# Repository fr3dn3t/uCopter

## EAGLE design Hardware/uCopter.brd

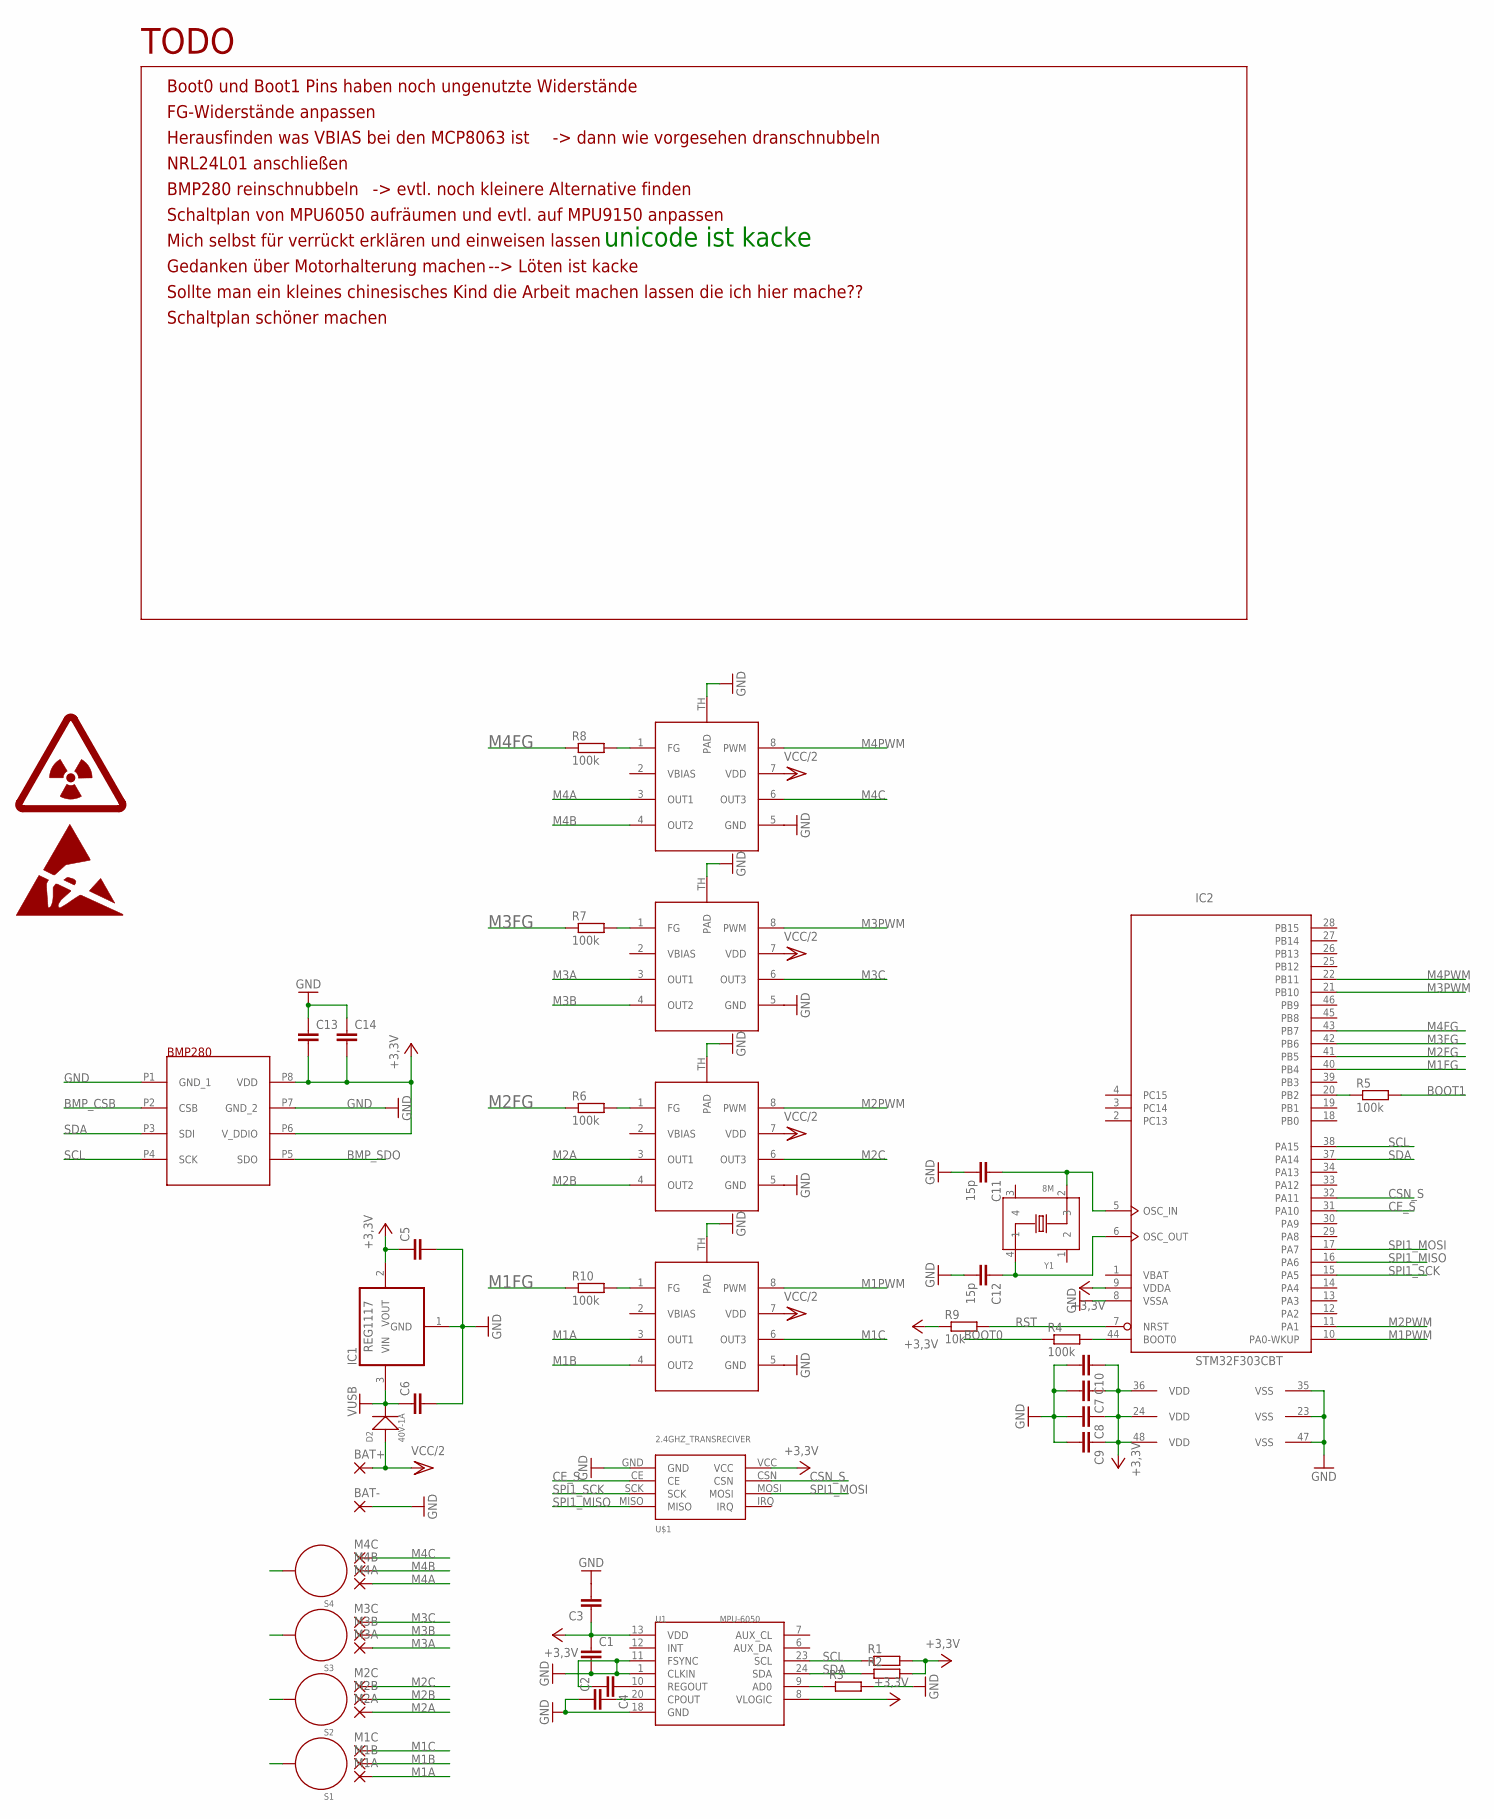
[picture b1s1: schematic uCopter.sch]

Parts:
BAT+: SMD2; SMD1,27-2,54
BAT-: SMD2; SMD1,27-2,54
C1, C2, C3, C4, C7, C8, C9, C10, C13, C14: C-EUC0402; C0402
C5, C6: C-EUC0603; C0603
C11, C12: 15p; C0402
D2: 40V-1A; DO-214AC
IC1: REG1117; SOT223
IC2: STM32F303CBT; LQFP48
M1A, M1B, M1C, M2A, M2B, M2C, M3A, M3B, M3C, M4A, M4B, M4C: 2,15/1,0
R1, R2, R3: R-EU_R0402; R0402
R4, R5, R6, R7, R8, R10: 100k; R0402
R9: 10k; R0402
S1, S2, S3, S4: STANDOFF_ELECTRICAL; STANDOFF-ELECTRICAL
T1: BMP280
U1: MPU-6050; QFN24G-0.5-4X4MM
U$1: 2.4GHZ_TRANSRECIVER
U$6, U$7, U$8, U$9: MCP8063; DFN8-4X4
Y1: 8M; X4-SMD-3.2X2.5X0.7MM

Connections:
+3,3V: C1.1, C3.1, C5.1, C7.1, C8.1, C9.1, C10.1, C13.2, C14.2, IC1.2 (VOUT), IC2.9 (VDDA), IC2.24 (VDD), IC2.36 (VDD), IC2.48 (VDD), R1.2, R2.2, R9.1, T1.P6 (V_DDIO), T1.P8 (VDD), U1.8 (VLOGIC), U1.13 (VDD), U$1.VCC
BMP_CSB: T1.P2 (CSB)
BMP_SDO: T1.P5 (SDO)
BOOT0: R4.1
BOOT1: R5.2
CE_S: IC2.31 (PA10), U$1.CE
CSN_S: IC2.32 (PA11), U$1.CSN
GND: BAT-.1, C1.2, C2.1, C3.2, C4.2, C5.2, C6.2, C7.2, C8.2, C9.2, C10.2, C11.2, C12.2, C13.1, C14.1, IC1.1 (GND), IC2.8 (VSSA), IC2.23 (VSS), IC2.35 (VSS), IC2.47 (VSS), R3.2, T1.P1 (GND_1), T1.P7 (GND_2), U1.1 (CLKIN), U1.11 (FSYNC), U1.18 (GND), U$1.GND, U$6.5 (GND), U$6.TH (PAD), U$7.5 (GND), U$7.TH (PAD), U$8.5 (GND), U$8.TH (PAD), U$9.5 (GND), U$9.TH (PAD)
M1A: M1A.1, U$6.3 (OUT1)
M1B: M1B.1, U$6.4 (OUT2)
M1C: M1C.1, U$6.6 (OUT3)
M1FG: IC2.40 (PB4), R10.1
M1PWM: IC2.10 (PA0-WKUP), U$6.8 (PWM)
M2A: M2A.1, U$7.3 (OUT1)
M2B: M2B.1, U$7.4 (OUT2)
M2C: M2C.1, U$7.6 (OUT3)
M2FG: IC2.41 (PB5), R6.1
M2PWM: IC2.11 (PA1), U$7.8 (PWM)
M3A: M3A.1, U$8.3 (OUT1)
M3B: M3B.1, U$8.4 (OUT2)
M3C: M3C.1, U$8.6 (OUT3)
M3FG: IC2.42 (PB6), R7.1
M3PWM: IC2.21 (PB10), U$8.8 (PWM)
M4A: M4A.1, U$9.3 (OUT1)
M4B: M4B.1, U$9.4 (OUT2)
M4C: M4C.1, U$9.6 (OUT3)
M4FG: IC2.43 (PB7), R8.1
M4PWM: IC2.22 (PB11), U$9.8 (PWM)
unnamed: R7.2, U$8.1 (FG)
unnamed: R8.2, U$9.1 (FG)
unnamed: C4.1, U1.10 (REGOUT)
unnamed: C2.2, U1.20 (CPOUT)
unnamed: R3.1, U1.9 (AD0)
unnamed: IC2.44 (BOOT0), R4.2
unnamed: IC2.20 (PB2), R5.1
unnamed: R10.2, U$6.1 (FG)
unnamed: C12.1, IC2.6 (OSC_OUT), Y1.4 (1)
unnamed: R6.2, U$7.1 (FG)
unnamed: C11.1, IC2.5 (OSC_IN), Y1.2 (3)
RST: IC2.7 (NRST), R9.2
SCL: IC2.38 (PA15), R1.1, T1.P4 (SCK), U1.23 (SCL)
SDA: IC2.37 (PA14), R2.1, T1.P3 (SDI), U1.24 (SDA)
SPI1_MISO: IC2.16 (PA6), U$1.MISO
SPI1_MOSI: IC2.17 (PA7), U$1.MOSI
SPI1_SCK: IC2.15 (PA5), U$1.SCK
VBAT: IC2.1 (VBAT)
VCC/2: BAT+.1, D2.1 (+), U$6.7 (VDD), U$7.7 (VDD), U$8.7 (VDD), U$9.7 (VDD)
VUSB: C6.1, D2.2 (-), IC1.3 (VIN)

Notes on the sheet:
Boot0 und Boot1 Pins haben noch ungenutzte Widerstände
FG-Widerstände anpassen
Herausfinden was VBIAS bei den MCP8063 ist
TODO
NRL24L01 anschließen
BMP280 reinschnubbeln
Schaltplan von MPU6050 aufräumen und evtl. auf MPU9150 anpassen
-> evtl. noch kleinere Alternative finden
Mich selbst für verrückt erklären und einweisen lassen
Gedanken über Motorhalterung machen
-> dann wie vorgesehen dranschnubbeln
--> Löten ist kacke
Sollte man ein kleines chinesisches Kind die Arbeit machen lassen die ich hier mache??
Schaltplan schöner machen
unicode ist kacke

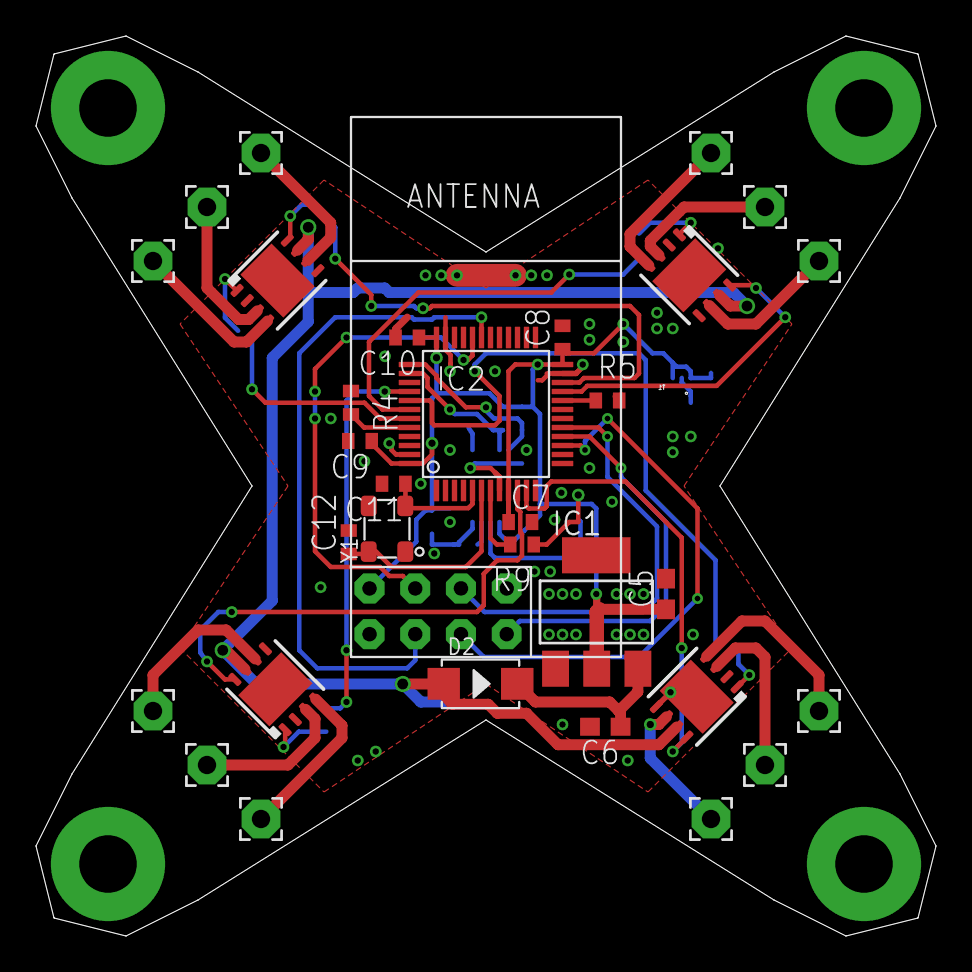
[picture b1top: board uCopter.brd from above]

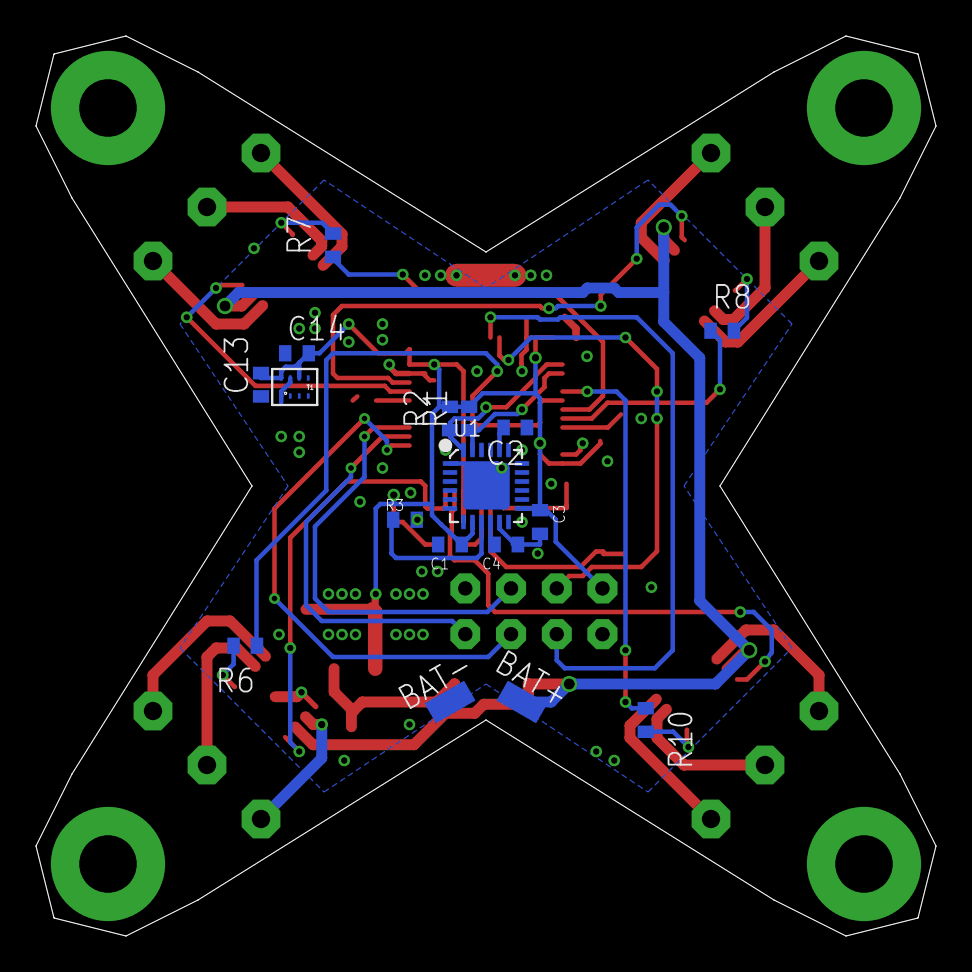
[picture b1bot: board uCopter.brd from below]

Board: 2 copper layers, 49.9 x 49.9 mm, 53 parts (17 on the bottom side), 43 nets.

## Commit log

2016-05-14 Removed unused files
2016-06-11 VERALTETE HARDWARE DIE NIE FUNKTIONIEREN WIRD!! NUR FÜR FREDERKIK!!!!! BITTESCHÖN \o\ \o/ /o/

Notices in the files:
parts and their libraries:
SparkFun-Electromechanical: Licensing: Creative Commons ShareAlike 4.0 International - https://creativecommons.org/licenses/by-sa/4.0
supply0: Copyright (C) 2007, Bob Starr
